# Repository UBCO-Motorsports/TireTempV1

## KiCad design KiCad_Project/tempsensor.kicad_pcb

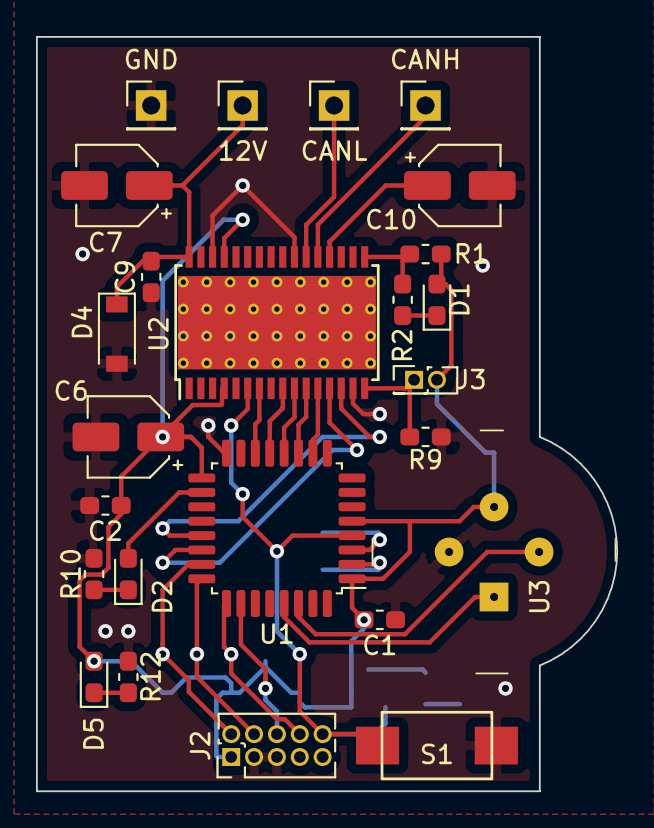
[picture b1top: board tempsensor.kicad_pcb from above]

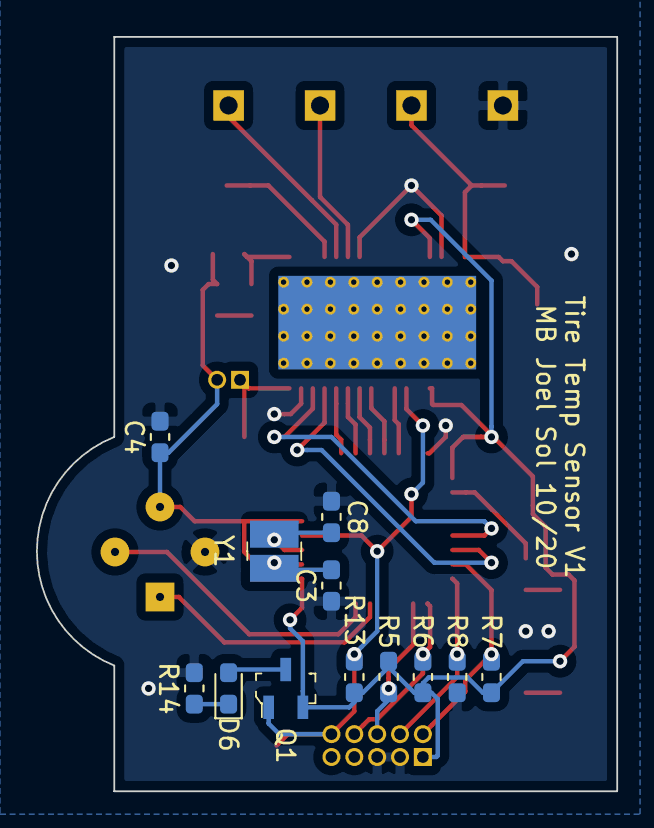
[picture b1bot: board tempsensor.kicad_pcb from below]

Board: 2 copper layers, 32.2 x 41.9 mm, 37 parts (12 on the bottom side), 30 nets.

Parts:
12V: Conn_01x01_Male; PinHeader_1x01_P2.54mm_Vertical
C1, C2, C4, C9: 100n; C_0603_1608Metric_Pad1.05x0.95mm_HandSolder
C3, C8: 8pF; C_0603_1608Metric_Pad1.05x0.95mm_HandSolder
C6, C7, C10: 10u; CP_Elec_4x5.4
CANH: Conn_01x01_Male; PinHeader_1x01_P2.54mm_Vertical
CANL: Conn_01x01_Male; PinHeader_1x01_P2.54mm_Vertical
D1, D6: LEDR; LED_0603_1608Metric_Pad1.05x0.95mm_HandSolder
D2, D5: LEDG; LED_0603_1608Metric_Pad1.05x0.95mm_HandSolder
D4: 30v; D_SOD-123
GND: Conn_01x01_Male; PinHeader_1x01_P2.54mm_Vertical
J2: SWD; PinHeader_2x05_P1.27mm_Vertical
J3: WD_Disable; PinHeader_2x01_P1.27mm_Vertical
Q1: BSS84; SOT-23-3
R1, R5, R6, R7, R8, R13: 10k; R_0603_1608Metric_Pad1.05x0.95mm_HandSolder
R2, R10, R12, R14: 220; R_0603_1608Metric_Pad1.05x0.95mm_HandSolder
R9: 1.3k; R_0603_1608Metric_Pad1.05x0.95mm_HandSolder
S1: RESET; PTS636 SK25F SMTR LFS
U1: STM32F303K8Tx; LQFP-32_7x7mm_P0.8mm
U2: UJA1075A; HTSSOP-32-1EP_6.1x11mm_P0.65mm_EP5.2x11mm_Mask4.11x4.36mm_T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
U3: MLX90614ESF-BAA-000-TU; TO-39-4
Y1: 8Mhz; SMD-2_3.2x2.5mm

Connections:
+3V3: C1.2, C2.1, C4.1, C6.1, D1.2, D5.2, J2.1, J3.2, Q1.2, R1.1, R5.1, R6.1, R7.1, R13.1, U1.1, U1.5, U1.17, U2.4, U2.29, U3.3
+12V: 12V.1, C7.1, C9.2, D4.1, U2.32
CANH: CANH.1, U2.21
CANL: CANL.1, U2.22
CAN_RX: U1.21, U2.14
CAN_TX: U1.22, U2.13
GND: C1.1, C2.2, C3.1, C4.2, C6.2, C7.2, C8.1, C9.1, C10.2, D4.2, GND.1, J2.3, J2.5, R8.2, R9.2, R10.1, R12.1, R14.2, S1.2, U1.16, U1.32, U2.15, U2.23, U2.30, U3.4
I2C_SCL: U1.29, U3.1
I2C_SDA: U1.30, U3.2
LIMP: R1.2, R2.2, U2.17
MISO: U1.12, U2.10
MOSI: U1.13, U2.9
unnamed: C10.1, U2.20
unnamed: D1.1, R2.1
unnamed: D2.1, R10.2
unnamed: D5.1, R12.2
unnamed: D6.1, R14.1
unnamed: D6.2, Q1.3
PA8: D2.2, U1.18
RCC_OSC_IN: C3.2, U1.2, Y1.1
RCC_OSC_OUT: C8.2, U1.3, Y1.2
RESET: J2.10, Q1.1, R13.2, S1.1, U1.4, U2.6
SBC_INTN: U1.14, U2.7
SCK: U1.11, U2.11
SCSN: U1.10, U2.12
SWDCLK: J2.4, R8.1, U1.24
SWDIO: J2.2, R7.2, U1.23
SWO: J2.6, R6.2, U1.26
TDI: J2.8, R5.2, U1.25
WD_OFF: J3.1, R9.1, U2.16

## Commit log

2020-10-15 Added PCB
2020-10-15 Rename
2020-10-22 Updated board traces
2020-10-23 Final Version
